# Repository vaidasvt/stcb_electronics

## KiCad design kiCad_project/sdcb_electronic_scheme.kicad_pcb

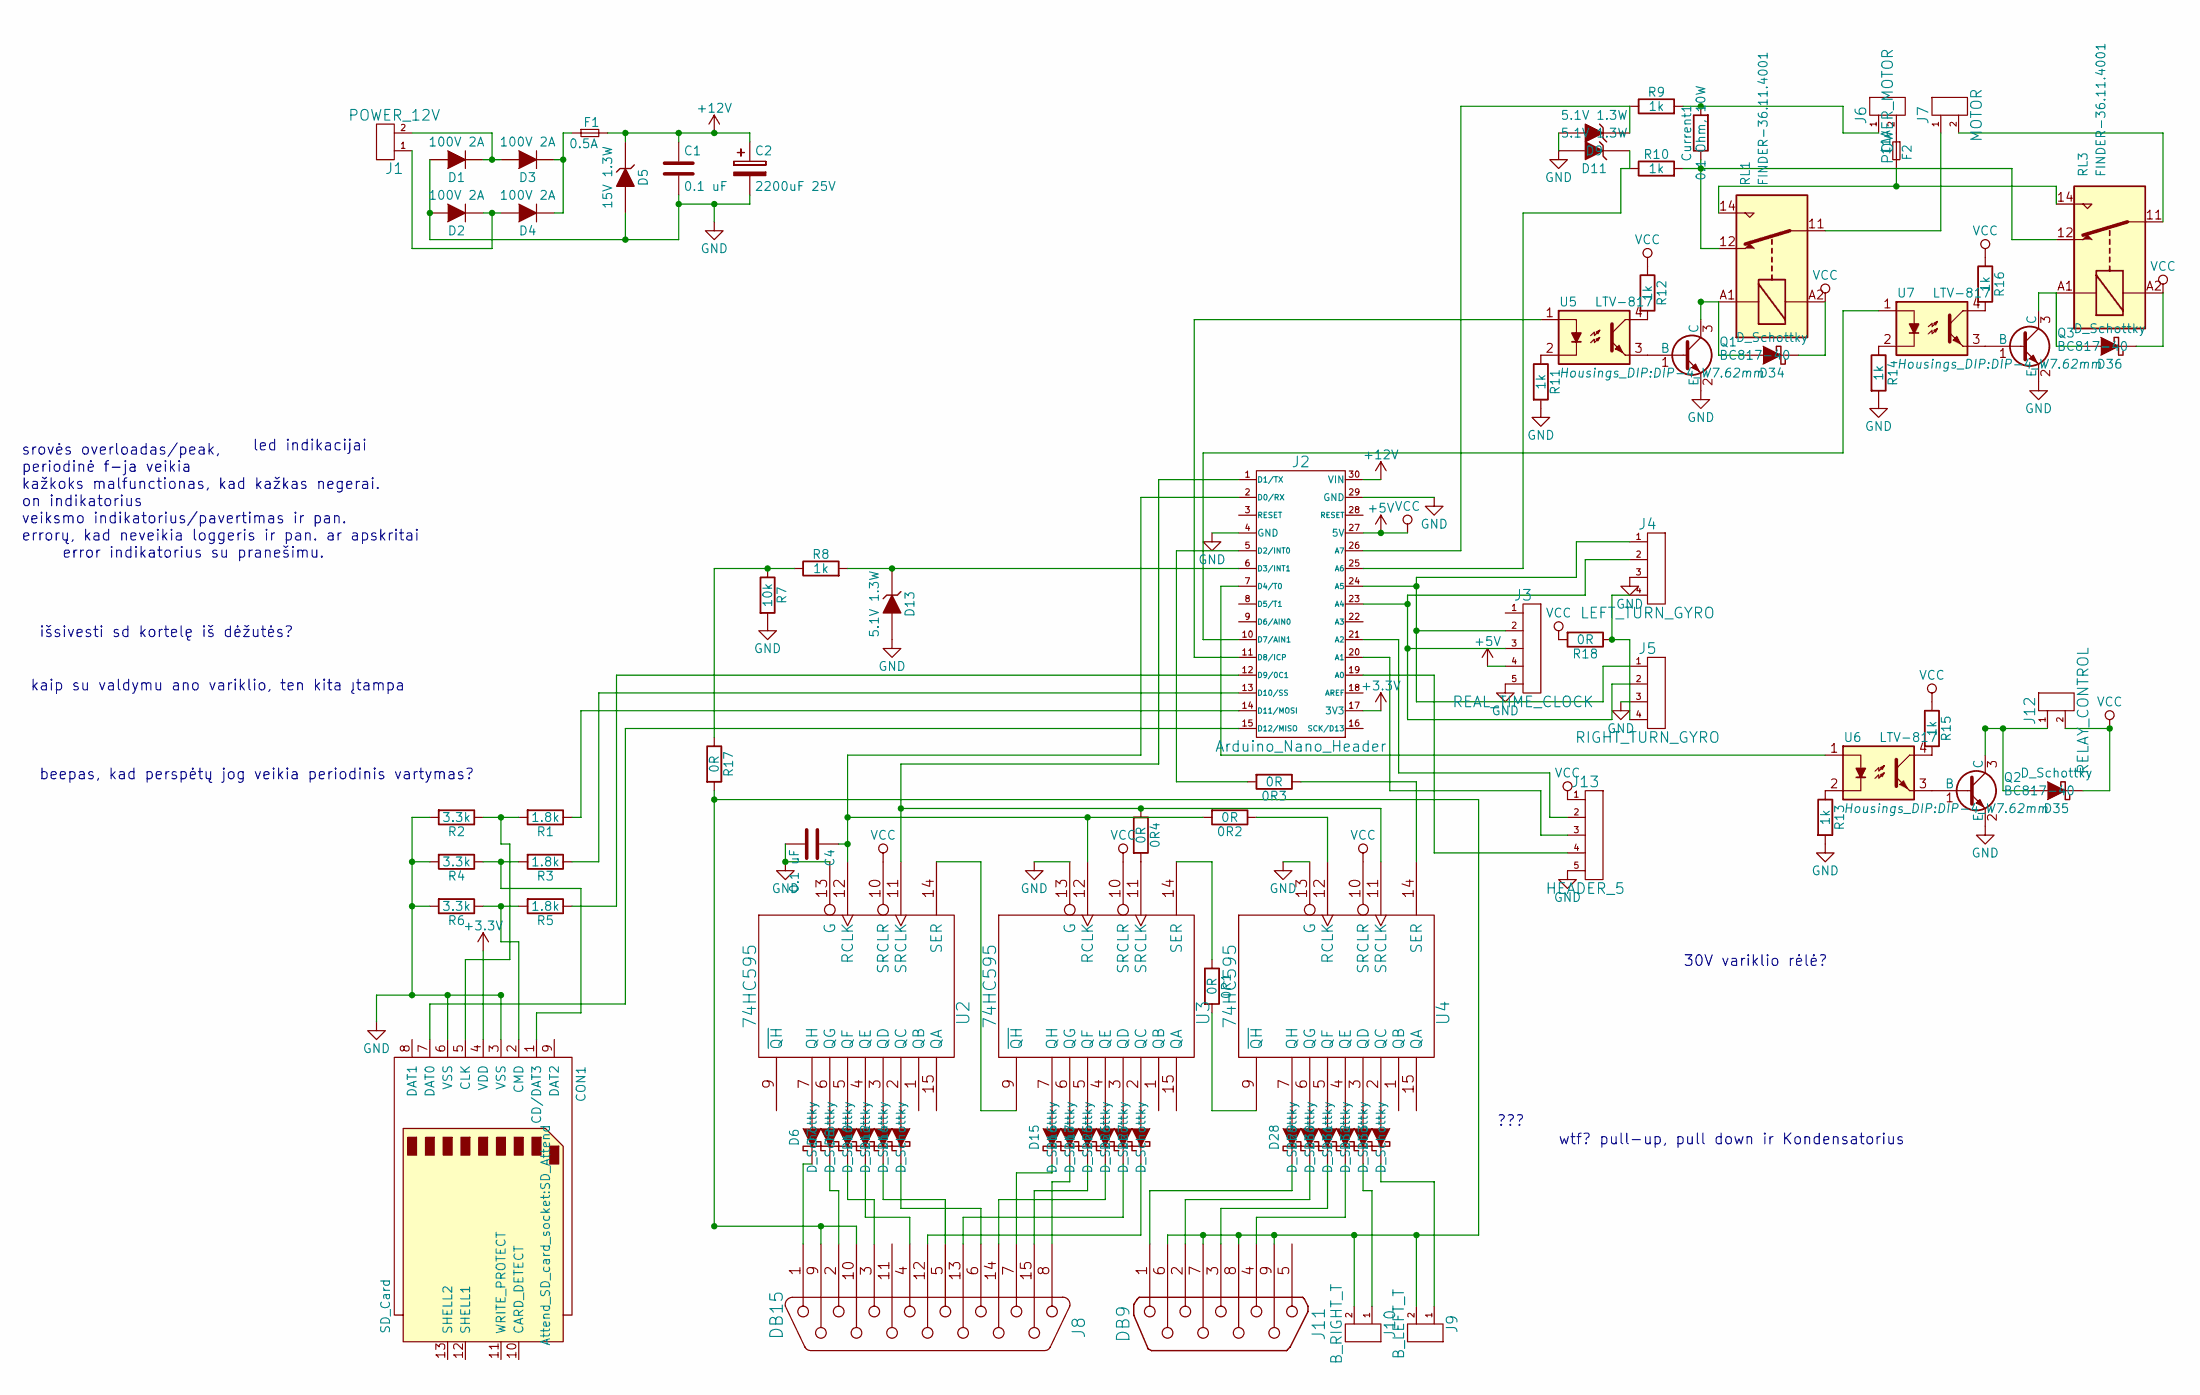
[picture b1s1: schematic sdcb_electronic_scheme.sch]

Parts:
0R1, 0R2, 0R3, 0R4: 0R; Resistor_Horizontal_RM10mm
C1, C4: 0.1 uF; C_Disc_D6_P5
C2: 2200uF 25V; Elko_vert_25x14mm_RM5_CopperClear
CON1: SD_Card; SD_Attend
Current1: 0.1 Ohm, 10W; Resistor_Horizontal_RM15mm
D1, D2, D3, D4: 100V 2A; Diode_DO-201AD_Horizontal_RM15
D5: 15V 1.3W; D3
D6, D7, D8, D10, D12, D14, D15, D16, D17, D25, D26, D27, D28, D29, D30, D31, D34, D35, D36: D_Schottky; Diode_DO-41_SOD81_Horizontal_RM10
D9, D11, D13: 5.1V 1.3W; D3
D32, D33: D_Schottky; Diode_DO-41_SOD81_Horizontal_RM10_SMALLER
F1: 0.5A; fuse_05A_slot
F2: 11A; fuse_05A_slot
J1: POWER_12V; AK300-2
J2: Arduino_Nano_Header; arduino_mini
J3: REAL_TIME_CLOCK; Pin_Header_Straight_1x05
J4: LEFT_TURN_GYRO; Pin_Header_Straight_1x05
J5: RIGHT_TURN_GYRO; Pin_Header_Straight_1x05
J6: POWER_MOTOR; AK300-2
J7: MOTOR; AK300-2
J8: DB15; DB15FC
J9: B_LEFT_T; Pin_Header_Straight_2x01
J10: B_RIGHT_T; Pin_Header_Straight_2x01
J11: DB9; DB9FC
J12: RELAY_CONTROL; Pin_Header_Straight_1x02
J13: HEADER_5; Pin_Header_Straight_1x05
Q1, Q2: BC817-40; TO-92_Molded_Wide_Oval
Q3: BC817-40; TO-92_Inline_Wide
R1: 1.8k; Resistor_Horizontal_RM15mm
R2, R4, R6: 3.3k; Resistor_Horizontal_RM10mm
R3, R5: 1.8k; Resistor_Horizontal_RM10mm
R7: 10k; Resistor_Horizontal_RM10mm
R8, R9, R10, R11, R12, R13, R14, R15, R16: 1k; Resistor_Horizontal_RM10mm
R17, R18: 0R; Resistor_Horizontal_RM15mm
RL1, RL3: FINDER-36.11.4001; sun_hold_scb1m1240
U2, U3, U4: 74HC595; DIP-16_W7.62mm_LongPads
U5, U6, U7: LTV-817; DIP-4_W7.62mm

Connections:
+3V3: CON1.4 (VDD), J2.17 (3V3)
+12V: C1.1, C2.1, D5.1 (K), F1.2, J2.30 (VIN)
GND: C1.2, C2.2, C4.2, CON1.3 (VSS), CON1.6 (VSS), D1.2 (A), D2.2 (A), D5.2 (A), D9.2 (A), D11.2 (A), D13.2 (A), J2.4 (GND), J2.29 (GND), J3.5, J4.3, J5.3, J13.5, Q1.2 (E), Q2.2 (E), Q3.2 (E), R2.2, R4.2, R6.2, R7.2, R11.2, R13.2, R14.2, U2.8 (GND), U2.13 (G), U3.8 (GND), U3.13 (G), U4.8 (GND), U4.13 (G); also elsewhere on the board
unnamed: 0R1.1, U3.14 (SER)
unnamed: 0R1.2, U4.9 (~QH)
unnamed: 0R2.1, U4.12 (RCLK)
unnamed: 0R2.2, C4.1, J2.2 (D0/RX), U2.12 (RCLK), U3.12 (RCLK)
unnamed: 0R3.1, U4.14 (SER)
unnamed: 0R3.2, J2.5 (D2/INT0)
unnamed: 0R4.1, J2.1 (D1/TX), U2.11 (SRCLK), U4.11 (SRCLK)
unnamed: 0R4.2, U3.11 (SRCLK)
unnamed: CON1.1 (CD/DAT3), R3.2, R4.1
unnamed: CON1.2 (CMD), R5.2, R6.1
unnamed: CON1.5 (CLK), R1.2, R2.1
unnamed: CON1.7 (DAT0), J2.15 (D12/MISO)
unnamed: Current1.1, R10.2, RL1.12, RL3.12
unnamed: Current1.2, J6.1, R9.2
unnamed: D1.1 (K), D3.2 (A), J1.2
unnamed: D2.1 (K), D4.2 (A), J1.1
unnamed: D3.1 (K), D4.1 (K), F1.1
unnamed: D6.1 (K), J8.1
unnamed: D6.2 (A), U2.7 (QH)
unnamed: D7.1 (K), J8.2
unnamed: D7.2 (A), U2.6 (QG)
unnamed: D8.1 (K), J8.3
unnamed: D8.2 (A), U2.5 (QF)
unnamed: D9.1 (K), J2.26 (A7), R9.1
unnamed: D10.1 (K), J8.4
unnamed: D10.2 (A), U2.4 (QE)
unnamed: D11.1 (K), J2.25 (A6), R10.1
unnamed: D12.1 (K), J8.5
unnamed: D12.2 (A), U2.3 (QD)
unnamed: D13.1 (K), J2.6 (D3/INT1), R8.2
unnamed: D14.1 (K), J8.6
unnamed: D14.2 (A), U2.2 (QC)
unnamed: D15.1 (K), J8.7
unnamed: D15.2 (A), U3.7 (QH)
unnamed: D16.1 (K), J8.8
unnamed: D16.2 (A), U3.6 (QG)
unnamed: D17.1 (K), J8.15
unnamed: D17.2 (A), U3.5 (QF)
unnamed: D25.1 (K), J8.14
unnamed: D25.2 (A), U3.4 (QE)
unnamed: D26.1 (K), J8.13
unnamed: D26.2 (A), U3.3 (QD)
unnamed: D27.1 (K), J8.12
unnamed: D27.2 (A), U3.2 (QC)
unnamed: D28.1 (K), J11.1
unnamed: D28.2 (A), U4.7 (QH)
unnamed: D29.1 (K), J11.2
unnamed: D29.2 (A), U4.6 (QG)
unnamed: D30.1 (K), J11.3
unnamed: D30.2 (A), U4.5 (QF)
unnamed: D31.1 (K), J11.4
unnamed: D31.2 (A), U4.4 (QE)
unnamed: D32.1 (K), J10.1
unnamed: D32.2 (A), U4.3 (QD)
unnamed: D33.1 (K), J9.1
unnamed: D33.2 (A), U4.2 (QC)
unnamed: D34.2 (A), Q1.3 (C), RL1.A1
unnamed: D35.2 (A), J12.1, Q2.3 (C)
unnamed: D36.2 (A), Q3.3 (C), RL3.A1
unnamed: F2.1, J6.2
unnamed: F2.2, RL1.14, RL3.14
unnamed: J2.7 (D4/T0), U6.1
unnamed: J2.10 (D7/AIN1), U7.1
unnamed: J2.11 (D8/ICP), U5.1
unnamed: J2.12 (D9/0C1), R5.1
unnamed: J2.13 (D10/SS), R3.1
unnamed: J2.14 (D11/MOSI), R1.1
unnamed: J2.23 (A4), J3.3, J4.2, J5.2
unnamed: J2.24 (A5), J3.2, J4.1, J5.1
unnamed: J7.1, RL1.11
unnamed: J7.2, RL3.11
unnamed: J8.9, J8.10, J9.2, J10.2, J11.6, J11.7, J11.8, J11.9, R17.2
unnamed: J2.21 (A2), J13.2
unnamed: J2.20 (A1), J13.3
unnamed: J2.19 (A0), J13.4
unnamed: Q1.1 (B), U5.3
unnamed: Q2.1 (B), U6.3
unnamed: Q3.1 (B), U7.3
unnamed: R11.1, U5.2
unnamed: R12.2, U5.4
unnamed: R13.1, U6.2
unnamed: R14.1, U7.2
unnamed: R15.2, U6.4
unnamed: R16.2, U7.4
unnamed: R7.1, R8.1, R17.1
unnamed: U2.14 (SER), U3.9 (~QH)

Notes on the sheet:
led indikacijai
srovės overloadas/peak, periodinė f-ja veikia kažkoks malfunctionas, kad kažkas negerai. on indikatorius veiksmo indikatorius/pavertimas ir pan. errorų, kad neveikia loggeris ir pan. ar apskritai error indikatorius su pranešimu.
kaip su valdymu ano variklio, ten kita įtampa
išsivesti sd kortelę iš dėžutės?
beepas, kad perspėtų jog veikia periodinis vartymas?
wtf? pull-up, pull down ir Kondensatorius
???
30V variklio rėlė?

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
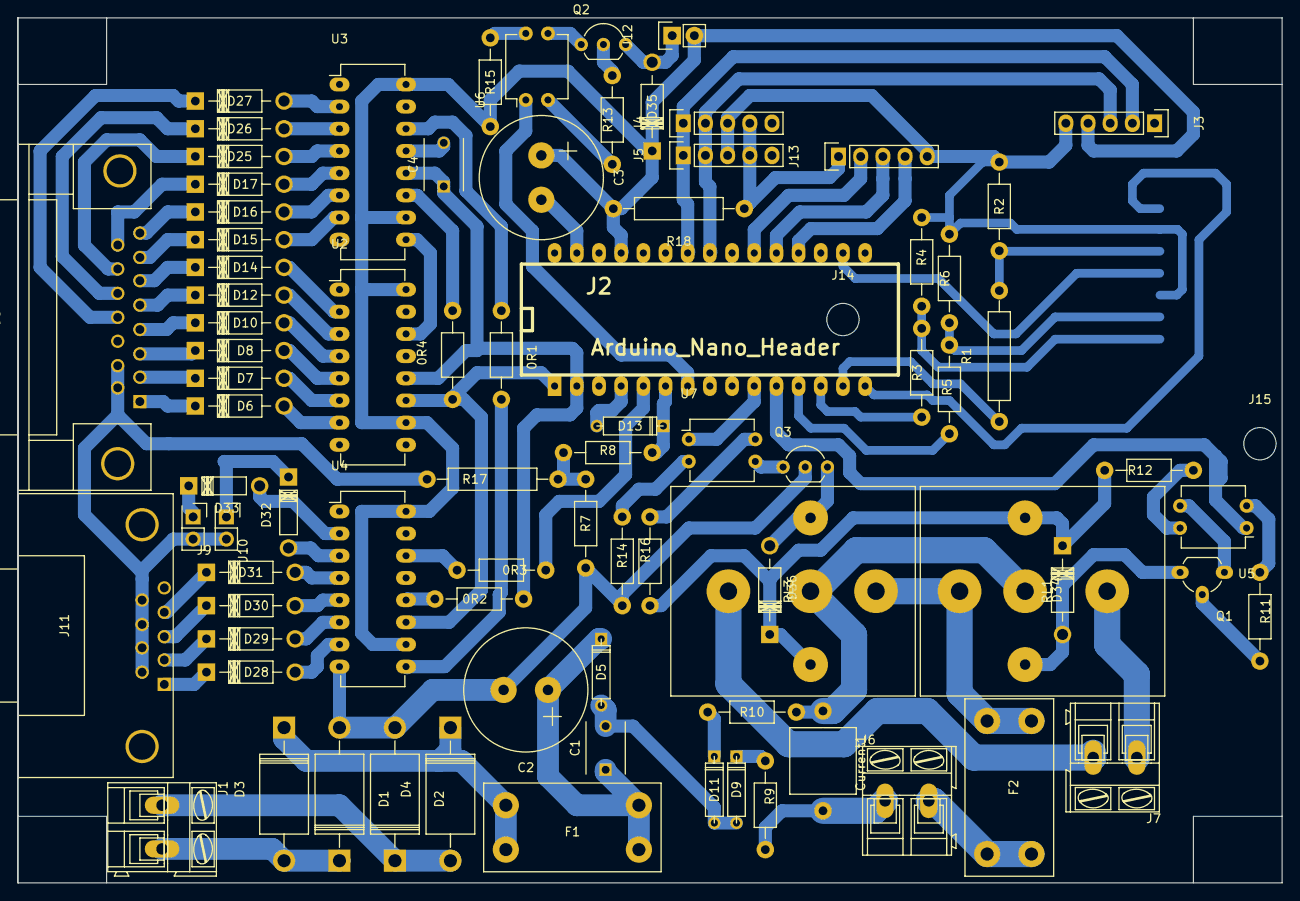
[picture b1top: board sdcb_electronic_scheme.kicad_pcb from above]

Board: 2 copper layers, 144.8 x 99.1 mm, 85 parts (1 on the bottom side), 90 nets.

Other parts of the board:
C3: 2200uF >6.3V; Elko_vert_25x14mm_RM5_CopperClear
J14, J15: HEADER_1; MountingHole_3-7mm

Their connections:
GND: C3.2, J14.1, J15.1; also elsewhere on the board

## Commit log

2015-08-04 adding README FILE
2015-08-04 Added project directory and .gitignore
2015-08-04 Added libs
2015-08-04 refactoring power rectification and smoothing circuit
2015-08-05 Buzzer lib
2015-08-05 Rescue lib
2015-08-06 Schematics updated
2015-08-06 PCB v1
2015-08-07 PCB v2
2015-08-08 39 left39 left39 left
2015-08-09 LEDs separated
2015-08-09 Varžtai IN
2015-08-09 LED project
